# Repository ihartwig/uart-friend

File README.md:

# uart-friend(s)

A collection of USB-UART adapters and adapter-adapters

[uart-friend](uart-friend): FTDI Friend like Micro-USB to TTL-UART bridge based on the CY7C65213 (or FT232R)
<br />

[uart-friend-c](uart-friend-c): USB-C plug verison of uart-friend - look, no cables!
<br />

[uart-friend-232](uart-friend-232): An RS232 levels and connector adapter for uart-friend
<br />

[uart-friend2-usb](uart-friend2-usb): A 2-usb-port RP2040 dev board to create a virtual uart bridge with usb
<br />
<br />

[swd-pogo-pins](swd-pogo-pins): (WIP) Adapter for TC2030 like footprint to for SPI programming

The projects in this repository need KiCAD 7 or later to open them.

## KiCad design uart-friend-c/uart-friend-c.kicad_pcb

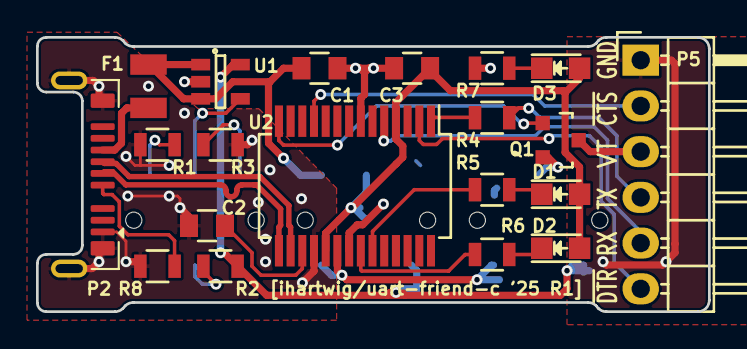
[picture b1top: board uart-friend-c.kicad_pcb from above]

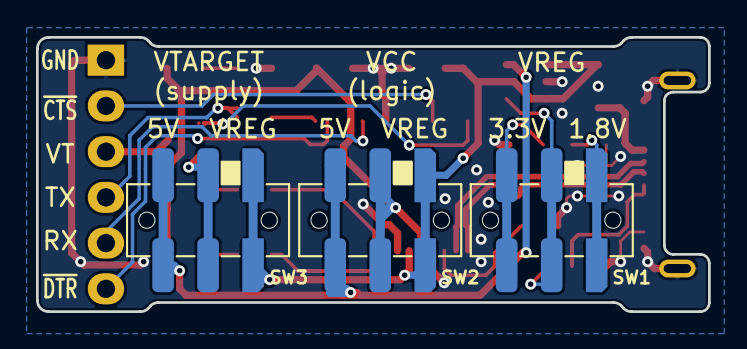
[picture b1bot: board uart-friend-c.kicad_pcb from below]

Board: 2 copper layers, 37.3 x 15.2 mm, 23 parts (3 on the bottom side), 25 nets.

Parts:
C1, C2, C3: 1uF; C_0805
D1: TX; LED-0805
D2: RX; LED-0805
D3: PWR; LED-0805
F1: 500mA-1206; Fuse_SMD1206_Reflow
P2: USB_C_Plug_USB3.0_9P; USB_C_Plug_G-Switch_GT-USB-8016A_9P_TopMnt_Horizontal
P5: CONN_01X06; Pin_Header_Angled_1x06
Q1: Q_PMOS_GSD; SOT-23
R1: 75k; R_0805
R2: 24k; R_0805
R3: 30k; R_0805
R4: 10; R_0805
R5, R6, R7: 220; R_0805
R8: 5.1k; R_0805
SW1, SW2, SW3: JS202011JAQN; Switch_SPDT_P2.5mm_RA_SMD_8x9mm
U1: AP7365_ADJ_SOT-23-5; SOT-23-5
U2: CY7C65213-SSOP; SSOP-28_5.3x10.2mm_Pitch0.65mm

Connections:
+5V: C1.1, F1.2, SW2.1 (C), SW3.1 (C), U1.1 (VIN), U1.3 (EN), U2.20 (VCC)
/FB_1V8: R3.1, SW1.3 (A)
/FB_3V3: R1.1, SW1.1 (C)
/FB_SEL: R2.2, SW1.2 (B), U1.4 (ADJ)
/RXD: P5.5, U2.5 (RXD)
/TXD: P5.4, R4.2
/TXD_R: R4.1, U2.1 (TXD)
/USB_D+: P2.A6 (D+), U2.15 (USBDP)
/USB_D-: P2.A7 (D-), U2.16 (USBDM)
/USB_VBUS: F1.1, P2.A9 (VBUS)
/VREG: R2.1, SW2.3 (A), SW3.3 (A), U1.5 (VOUT)
/VTARGET: P5.3, Q1.3 (D)
/VTARGET_Q: Q1.2 (S), SW3.2 (B)
/~CTS: P5.2, U2.11 (~CTS)
/~DTR: P5.6, U2.2 (~DTR)
/~POWER: Q1.1 (G), U2.14 (GPIO3)
/~RXLED: R6.1, U2.22 (GPIO1)
/~TXLED: R5.1, U2.23 (GPIO0)
GND: C1.2, C2.2, C3.2, P2.A1 (GND), P2.SH1 (SHIELD), P5.1, R1.2, R3.2, R7.1, R8.2, U1.2 (GND), U2.7 (GND), U2.18 (GND), U2.21 (GND)
unnamed: D1.1 (K), R5.2
unnamed: D2.1 (K), R6.2
unnamed: D3.1 (K), R7.2
unnamed: P2.A5 (CC), R8.1
unnamed: C2.1, U2.17 (VCCD)
VCC: C3.1, D1.2 (A), D2.2 (A), D3.2 (A), SW2.2 (B), U2.4 (VCCIO), U2.19 (~RESET)

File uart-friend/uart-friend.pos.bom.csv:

Ref,Val,Package,PosX,PosY,Rot,Side,Mfg,Mfg Part No,Digikey Part No
C1,1uF,C_0805,12.065,15.24,0,top,Yageo,CC0805KKX7R7BB105,311-1365-1-ND
C2,1uF,C_0805,21.59,9.525,0,top,Yageo,CC0805KKX7R7BB105,311-1365-1-ND
C3,1uF,C_0805,17.145,15.24,180,top,Yageo,CC0805KKX7R7BB105,311-1365-1-ND
D1,TX,LED-0805,25.4,6.985,0,top,Osram,LG R971-KN-1,475-1410-1-ND
D2,RX,LED-0805,25.4,4.445,0,top,Osram,LG R971-KN-1,475-1410-1-ND
D3,PWR,LED-0805,25.4,15.24,0,top,Osram,LG R971-KN-1,475-1410-1-ND
F1,500mA-1206,Fuse_SMD1206_Ref,6.985,10.795,90,top,Bel Fuse,0ZCK0050FF2E,507-1813-1-ND
P1,USB_OTG,USB_Micro-B,2.54,8.255,270,top,Amphenol FCI,10118194-0001LF,609-4618-1-ND
Q1,Q_PMOS_GSD,SOT-23,25.4,10.795,270,top,Diodes,DMG2305UX-7,DMG2305UX-7DICT-ND
R1,75k,R_0805,3.81,14.605,90,top,Yageo,RC0805FR-0775KL,311-75.0KCRCT-ND
R2,24k,R_0805,6.985,5.08,90,top,Yageo,RC0805FR-0724KL,311-24.0KCRCT-ND
R3,30k,R_0805,1.27,14.605,90,top,Yageo,RC0805FR-0730KL,311-30.0KCRCT-ND
R4,10,R_0805,21.59,12.065,0,top,Yageo,RC0805JR-0710RL,311-10ARCT-ND
R5,220,R_0805,21.59,6.985,0,top,Yageo,RC0805JR-07220RL,311-220ARCT-ND
R6,220,R_0805,21.59,4.445,0,top,Yageo,RC0805JR-07220RL,311-220ARCT-ND
R7,220,R_0805,21.59,15.24,0,top,Yageo,RC0805JR-07220RL,311-220ARCT-ND
U1,AP7365_ADJ_SOT-2,SOT-23-5,6.985,14.605,0,top,Diodes,AP7365-WG-7,AP7365-WG-7DICT-ND
U2,CY7C65213-SSOP,SSOP-28_5.3x10.2,13.97,8.255,270,top,Cypress,CY7C65213-28PVXI,CY7C65213-28PVXI-ND

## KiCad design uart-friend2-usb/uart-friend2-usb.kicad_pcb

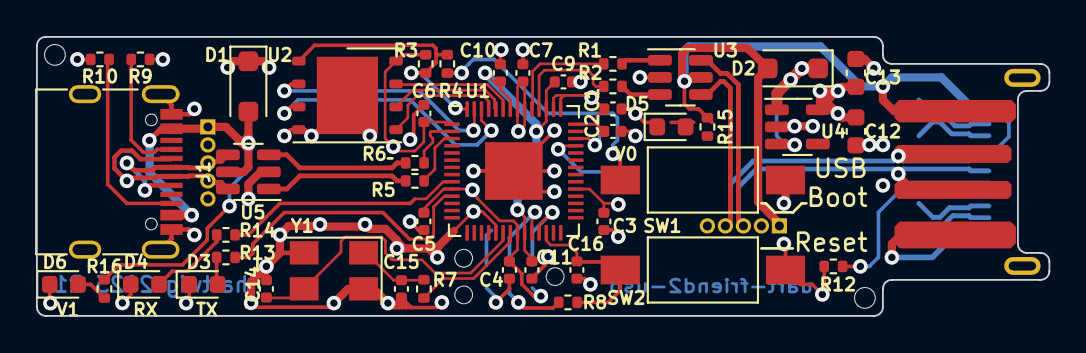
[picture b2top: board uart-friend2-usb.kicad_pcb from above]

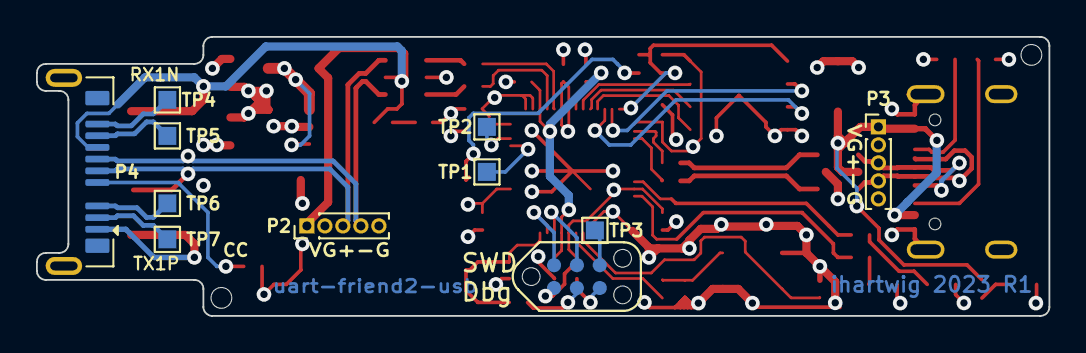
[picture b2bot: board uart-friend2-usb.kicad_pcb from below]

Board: 4 copper layers, 56.2 x 15.5 mm, 57 parts (11 on the bottom side), 48 nets.

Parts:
C1, C9: 1uF; C_0402_1005Metric
C2, C3, C4, C5, C6, C7, C10, C11, C16: 0.1uF; C_0402_1005Metric
C12, C13: 2.2uF; C_0603_1608Metric
C14, C15: 15pF; C_0402_1005Metric
D1, D2: RF071M2STR; D_SOD-123F
D3, D4: Yellow; LED_0603_1608Metric
D5, D6: Green; LED_0603_1608Metric
J1: USB_C_Receptacle_USB2.0; USB_C_Receptacle_G-Switch_GT-USB-7010ASV
J2: Conn_02x03_Odd_Even; TC2030-NL_SMALL
P1: USB_A_Plug_PCB; USB_A_Plug_PCB_Shorter_Pads
P2, P3: USB_C_Plug_USB2.0_16P; PinHeader_1x05_P1.00mm_Vertical
P4: USB_C_Plug_USB3.0_9P; USB_C_Plug_G-Switch_GT-USB-8016A_9P_TopMnt_Horizontal
R1, R2: 27; R_0402_1005Metric
R3, R8: 1k; R_0402_1005Metric
R4: 10k; R_0402_1005Metric
R5, R6: 22; R_0402_1005Metric
R7: 6.8k; R_0402_1005Metric
R9, R10, R12, R13, R14, R15, R16: 5.1k; R_0402_1005Metric
SW1: BOOT; SW_SPST_FSMSM
SW2: RST; SW_SPST_FSMSM
TP1, TP2, TP3, TP4, TP5, TP6, TP7: TestPoint; TestPoint_Pad_1.0x1.0mm
U1: RP2040; QFN-56-1EP_7x7mm_P0.4mm_EP3.2x3.2mm
U2: W25Q128JVPIQ; WSON-8-1EP_6x5mm_P1.27mm_EP3.4x4.3mm
U3, U5: WE-TVS-82400102; SOT-23-6
U4: AP7366-33W5-7; SOT-23-5
Y1: 12MHz; Crystal_SMD_5032-4Pin_5.0x3.2mm

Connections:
+3V3: C1.1, C2.1, C3.1, C4.1, C5.1, C6.1, C7.1, C12.1, C13.1, J2.1, R3.1, U1.1 (IOVDD), U1.10 (IOVDD), U1.22 (IOVDD), U1.33 (IOVDD), U1.42 (IOVDD), U1.43 (ADC_AVDD), U1.44 (VREG_IN), U1.48 (USB_VDD), U1.49 (IOVDD), U2.8 (VCC), U4.5 (OUT)
/ADC1: TP1.1, U1.39 (GPIO27_ADC1)
/ADC2: TP2.1, U1.40 (GPIO28_ADC2)
/J1_CC1: J1.A5 (CC1), R9.1
/J2_CC2: J1.B5 (CC2), R10.1
/LED_GPIO7: R14.1, U1.9 (GPIO7)
/LED_GPIO8: R13.1, U1.11 (GPIO8)
/P4_CC: P4.A5 (CC), R12.2
/SWD: J2.2, U1.25 (SWD)
/SWD_CLK: J2.4, U1.24 (SWCLK)
/SWD_OUT: J2.6, TP3.1
/SWD_RST: J2.3, R8.2
/U1_BOOT: R4.1, SW1.2
/U1_EEPROM_SCLK: U1.52 (QSPI_SCLK), U2.6 (CLK)
/U1_EEPROM_SD0: U1.53 (QSPI_SD0), U2.5 (DI(IO0))
/U1_EEPROM_SD1: U1.55 (QSPI_SD1), U2.2 (DO(IO1))
/U1_EEPROM_SD3: U1.51 (QSPI_SD3), U2.7 (IO3)
/U1_EEPROM_SS_L: R3.2, R4.2, U1.56 (QSPI_SS), U2.1 (~CS)
/U1_RUN: C16.1, R8.1, SW2.2, U1.26 (RUN)
/U1_XIN: C14.1, U1.20 (XIN), Y1.3
/U1_XOUT: R7.2, U1.21 (XOUT)
/U1_XOUT_R: C15.1, R7.1, Y1.1
/USB0_D_N: P1.2 (D-), P2.4 (D-), P4.A7 (D-), U3.4
/USB0_D_P: P1.3 (D+), P2.3 (D+), P4.A6 (D+), U3.6
/USB0_N: R2.2, U1.46 (USB_DM)
/USB0_P: R1.2, U1.47 (USB_DP)
/USB0_R_N: R2.1, U3.3
/USB0_R_P: R1.1, U3.1
/USB0_SSRX1_N: P4.B10 (RX1-), TP4.1
/USB0_SSRX1_P: P4.B11 (RX1+), TP5.1
/USB0_SSTX1_N: P4.A3 (TX1-), TP6.1
/USB0_SSTX1_P: P4.A2 (TX1+), TP7.1
/USB1_D_N: J1.A7 (D-), J1.B7 (D-), P3.4 (D-), U5.6
/USB1_D_P: J1.A6 (D+), J1.B6 (D+), P3.3 (D+), U5.4
/USB1_N: R5.1, U1.3 (GPIO1)
/USB1_P: R6.1, U1.2 (GPIO0)
/USB1_R_N: R5.2, U5.1
/USB1_R_P: R6.2, U5.3
/VBUS0: D2.2 (A), P1.1 (VBUS), P2.1 (VBUS), P4.A9 (VBUS), R15.1, U3.5
/VBUS1: D1.2 (A), J1.A4 (VBUS), J1.A9 (VBUS), J1.B4 (VBUS), J1.B9 (VBUS), P3.1 (VBUS), R16.1, U5.5
GND: C1.2, C2.2, C3.2, C4.2, C5.2, C6.2, C7.2, C9.2, C10.2, C11.2, C12.2, C13.2, C14.2, C15.2, C16.2, D3.1 (K), D4.1 (K), D5.1 (K), D6.1 (K), J1.A1 (GND), J1.A12 (GND), J1.B1 (GND), J1.B12 (GND), J1.S1 (SHIELD), J2.5, P1.4 (GND), P2.2 (GND), P2.5 (GND), P3.2 (GND), P3.5 (GND), P4.A1 (GND), R9.2, R10.2, R12.1, SW1.1, SW2.1, U1.19 (TESTEN), U1.57 (GND), U2.4 (GND), U2.9 (EP), U3.2, U4.2 (GND), U5.2, Y1.2, Y1.4
unnamed: D3.2 (A), R13.2
unnamed: D4.2 (A), R14.2
unnamed: D5.2 (A), R15.2
unnamed: D6.2 (A), R16.2
unnamed: U1.54 (QSPI_SD2), U2.3 (IO2)
VBUS: D1.1 (K), D2.1 (K), U4.1 (IN), U4.3 (EN)
VDD: C9.1, C10.1, C11.1, U1.23 (DVDD), U1.45 (VREG_VOUT), U1.50 (DVDD)

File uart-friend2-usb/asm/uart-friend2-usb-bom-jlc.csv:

Comment,Designator,Footprint,LCSC
"1uF","C1,C9","Capacitor_SMD:C_0402_1005Metric","C52923"
"2.2uF","C12,C13","Capacitor_SMD:C_0603_1608Metric","C23630"
"15pF","C14,C15","Capacitor_SMD:C_0402_1005Metric","C1548"
"0.1uF","C2,C3,C4,C5,C6,C7,C10,C11,C16","Capacitor_SMD:C_0402_1005Metric","C1525"
"RF071M2STR","D1,D2","Diode_SMD:D_SOD-123F","C78744"
"Yellow","D3,D4","LED_SMD:LED_0603_1608Metric","C72038"
"Green","D5,D6","LED_SMD:LED_0603_1608Metric","C72043"
"USB_C_Receptacle_USB2.0","J1","Connector_USB:USB_C_Receptacle_G-Switch_GT-USB-7010ASV","C2988369"
"USB_C_Plug_USB2.0_16P","P2,P3","Connector_PinHeader_1.00mm:PinHeader_1x05_P1.00mm_Vertical",""
"USB_C_Plug_USB3.0_9P","P4","uart-friend2-usb-special:USB_C_Plug_G-Switch_GT-USB-8016A_9P_TopMnt_Horizontal",""
"22","R1,R2,R5,R6","Resistor_SMD:R_0402_1005Metric","C25092"
"1k","R3,R8","Resistor_SMD:R_0402_1005Metric","C11702"
"10k","R4","Resistor_SMD:R_0402_1005Metric","C25744"
"6.8k","R7","Resistor_SMD:R_0402_1005Metric","C25917"
"5.1k","R9,R10,R12,R13,R14,R15,R16","Resistor_SMD:R_0402_1005Metric","C25905"
"BOOT","SW1","Button_Switch_SMD:SW_SPST_FSMSM","C2888955"
"RST","SW2","Button_Switch_SMD:SW_SPST_FSMSM","C2888955"
"RP2040","U1","Package_DFN_QFN:QFN-56-1EP_7x7mm_P0.4mm_EP3.2x3.2mm","C2040"
"W25Q128JVPIQ","U2","Package_SON:WSON-8-1EP_6x5mm_P1.27mm_EP3.4x4.3mm","C2803379"
"WE-TVS-82400102","U3,U5","Package_TO_SOT_SMD:SOT-23-6","C1975330"
"AP7366-33W5-7","U4","Package_TO_SOT_SMD:SOT-23-5","C526385"
"12MHz","Y1","Crystal:Crystal_SMD_5032-4Pin_5.0x3.2mm","C2149262"

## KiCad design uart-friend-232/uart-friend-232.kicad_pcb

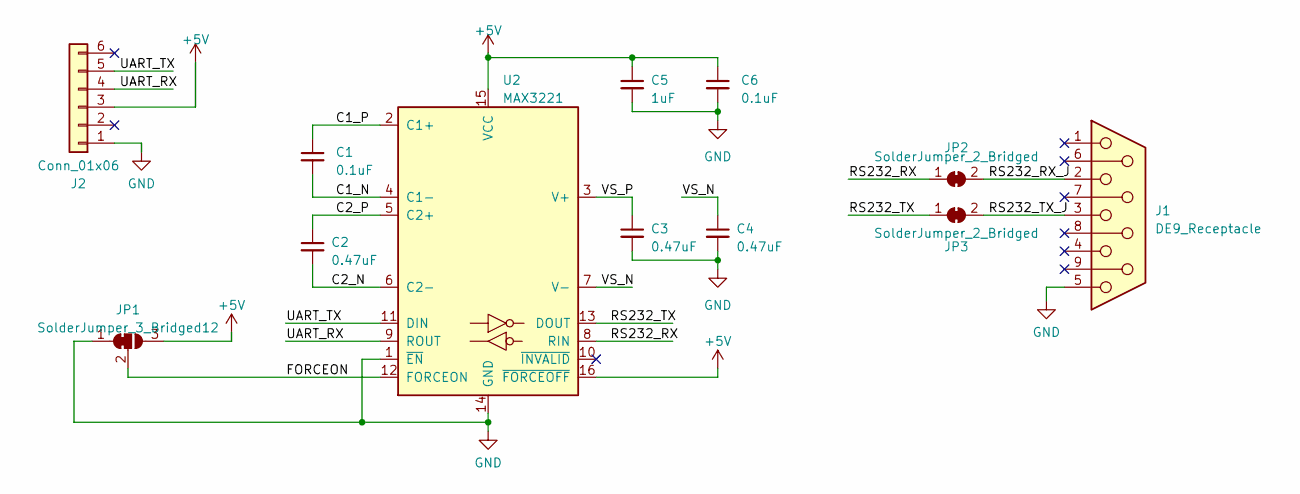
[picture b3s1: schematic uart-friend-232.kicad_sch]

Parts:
C1, C6: 0.1uF; C_0805_2012Metric
C2, C3, C4: 0.47uF; C_0805_2012Metric
C5: 1uF; C_0805_2012Metric
J1: DE9_Receptacle; DSUB-9_Female_EdgeMount_P2.77mm
J2: Conn_01x06; PinHeader_1x06_P2.54mm_Vertical
JP1: SolderJumper_3_Bridged12; SolderJumper-3_P1.3mm_Bridged12_RoundedPad1.0x1.5mm
JP2, JP3: SolderJumper_2_Bridged; SolderJumper-2_P1.3mm_Bridged_RoundedPad1.0x1.5mm
U2: MAX3221; TSSOP-16_4.4x5mm_P0.65mm

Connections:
+5V: C5.1, C6.1, J2.3, JP1.3 (B), U2.15 (VCC), U2.16 (~FORCEOFF)
/C1_N: C1.2, U2.4 (C1-)
/C1_P: C1.1, U2.2 (C1+)
/C2_N: C2.2, U2.6 (C2-)
/C2_P: C2.1, U2.5 (C2+)
/FORCEON: JP1.2 (C), U2.12 (FORCEON)
/RS232_RX: JP2.1 (A), U2.8 (RIN)
/RS232_RX_J: J1.2, JP2.2 (B)
/RS232_TX: JP3.1 (A), U2.13 (DOUT)
/RS232_TX_J: J1.3, JP3.2 (B)
/UART_RX: J2.4, U2.9 (ROUT)
/UART_TX: J2.5, U2.11 (DIN)
/VS_N: C4.1, U2.7 (V-)
/VS_P: C3.1, U2.3 (V+)
GND: C3.2, C4.2, C5.2, C6.2, J1.5, J2.1, JP1.1 (A), U2.1 (~EN), U2.14 (GND)

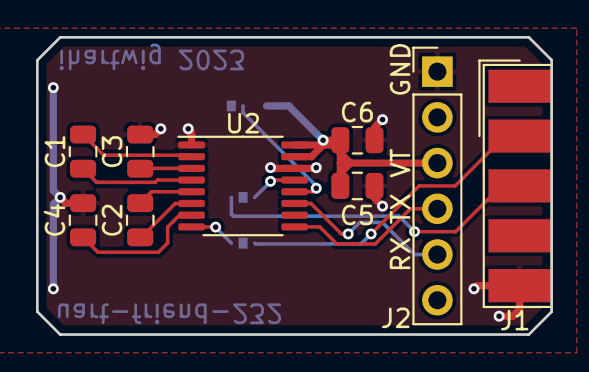
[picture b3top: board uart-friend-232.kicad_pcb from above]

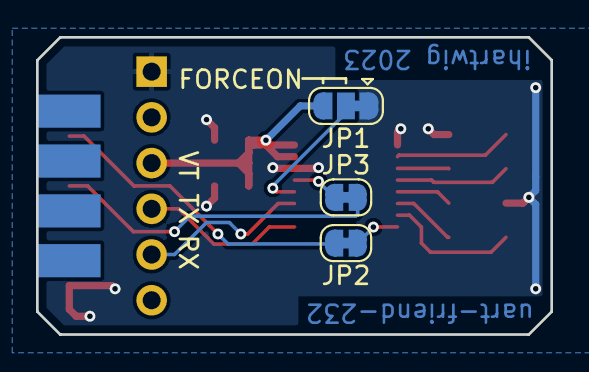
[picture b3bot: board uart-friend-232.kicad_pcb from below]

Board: 2 copper layers, 28.6 x 16.5 mm, 12 parts (3 on the bottom side), 15 nets.

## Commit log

2016-03-30 complete schematic and board
2016-06-19 update vias to 2:1 apr, make 2 up for production
2016-07-24 make single board gerbers, placement, and bom
2023-11-05 mv pcb uart-friend
2023-11-07 add uart-friend-232 rs232 adapter
2023-11-24 gitignore kicad backups
2023-12-03 add swd-pogo-pins sch
2023-12-08 most uart-friend2-usb footprints
2023-12-27 resolve uart-friend2-usb footprint issues
2023-12-29 uart-friend2-usb floorplan and some layout
2023-12-31 uart-friend2-usb R1 layout schematic metadata production files
2025-12-25 readme cleanup
2025-12-25 add uart-friend-c project
2025-12-26 add uart-friend-c R1 design
